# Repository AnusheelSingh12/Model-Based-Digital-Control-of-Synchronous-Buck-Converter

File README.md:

# Model-Based Design and HIL Deployment of a Cascade Digital Controller for a Synchronous Buck Converter on TI C2000 DSP

## Summer Research Internship

**Institution:** Indian Institute of Technology Guwahati

**Duration:** May 2026 – July 2026

---

# Overview

This repository documents my Summer Research Internship carried out at the Department of Electronics and Electrical Engineering, Indian Institute of Technology Guwahati.

The internship focused on the complete workflow involved in designing, simulating, implementing, and validating a digitally controlled synchronous buck converter using the Texas Instruments C2000 real-time digital signal processor platform.

Unlike repositories that present only the final implementation, this repository documents the complete engineering process, beginning with mathematical modeling and simulation, progressing through controller design, embedded firmware development, peripheral configuration, laboratory validation, and finally hardware deployment.

The project combines concepts from:

* Power Electronics
* Control Systems
* Embedded Systems
* Digital Signal Processing
* MATLAB & Simulink
* Simscape Electrical
* Real-Time Embedded Programming
* Hardware-in-the-Loop Development

---

# Project Objectives

The primary objectives of the internship were:

* Develop a high-fidelity digital twin of a synchronous buck converter.
* Design a cascaded digital controller consisting of outer voltage and inner current control loops.
* Learn the Texas Instruments C2000 development ecosystem.
* Implement embedded firmware using Code Composer Studio.
* Configure and validate DSP peripherals including GPIO, Timers, PWM, Interrupts, and ADC.
* Validate controller performance using laboratory instruments.
* Document the complete engineering workflow.

---

# Engineering Workflow

```text
Problem Definition
        │
        ▼
MATLAB Fundamentals
        │
        ▼
Simulink Fundamentals
        │
        ▼
Simscape Electrical
        │
        ▼
Digital Twin Development
        │
        ▼
Cascade PI Controller Design
        │
        ▼
Closed Loop Simulation
        │
        ▼
TI C2000 DSP Learning
        │
        ▼
GPIO
Interrupts
CPU Timers
PWM
ADC
        │
        ▼
Hardware Validation
        │
        ▼
Final System Integration
```

---

# Repository Structure

```text
IITG-DSP-Buck-Converter-Control/

├── 01_Internship_Overview/
│
├── 02_MATLAB_and_Simulink/
│
├── 03_Digital_Twin/
│
├── 04_Cascade_Controller/
│
├── 05_TI_C2000_DSP/
│   ├── GPIO/
│   ├── Interrupts/
│   ├── CPU_Timers/
│   ├── ePWM/
│   ├── ADC/
│
├── 06_Hardware_Setup/
│   ├── LaunchXL_F28379D/
│   ├── Oscilloscope/
│   ├── Function_Generator/
│
├── 07_Firmware/
│
├── 08_Simulation_Results/
│
├── 09_Final_Report/
│
├── Images/
│
├── Videos/
│
└── README.md
```

---

# Project Phases

## Phase 1 — Digital Twin Development

The first stage of the project focused on constructing a high-fidelity Simscape Electrical model of the synchronous buck converter.

Topics include:

* Converter topology
* MOSFET modelling
* Passive component modelling
* PWM generation
* Open-loop validation
* Converter analysis
* Duty-cycle experiments

---

## Phase 2 — Cascade Digital Controller

The second stage involved designing a cascaded digital controller.

Topics include:

* Voltage control loop
* Current control loop
* PI controller design
* Closed-loop regulation
* Controller tuning
* Performance analysis

---

## Phase 3 — TI C2000 DSP Development

The third stage focused on learning and implementing embedded firmware using the Texas Instruments C2000 platform.

Topics include:

* Code Composer Studio
* Project configuration
* GPIO
* Interrupts
* CPU Timers
* Enhanced PWM
* ADC
* Debugging
* Flash programming

---

## Phase 4 — Hardware Validation

The final stage focuses on validating both the firmware and control algorithms using laboratory equipment.

Topics include:

* Oscilloscope measurements
* Function generator experiments
* PWM verification
* ADC verification
* Peripheral testing
* System integration

---

# Software and Development Tools

MATLAB

Simulink

Simscape Electrical

Code Composer Studio

C2000Ware

Texas Instruments C2000 Driver Library

---

# Hardware Platform

Texas Instruments LaunchXL-F28379D

Texas Instruments C2000 DSP

Rigol Digital Oscilloscope

Function Generator

Host Computer

---

# Skills Developed

Throughout this internship I gained practical experience in:

* Model-Based Design
* Power Electronics
* Control Systems
* Digital Signal Processing
* MATLAB Programming
* Simulink Modelling
* Simscape Electrical
* Embedded C Programming
* TI C2000 Development
* Code Composer Studio
* GPIO Configuration
* Interrupt Programming
* CPU Timers
* PWM Generation
* ADC Configuration
* Oscilloscope Measurements
* Function Generator Operation
* Hardware Debugging
* Engineering Documentation

---

# Repository Navigation

| Section             | Description                                         |
| ------------------- | --------------------------------------------------- |
| Internship Overview | Internship objectives, timeline, and research scope |
| MATLAB and Simulink | Learning material and simulation fundamentals       |
| Digital Twin        | Simscape converter modelling                        |
| Cascade Controller  | Controller design and closed-loop simulation        |
| TI C2000 DSP        | Embedded firmware development                       |
| Hardware Setup      | Laboratory setup and instrumentation                |
| Firmware            | Embedded source code                                |
| Simulation Results  | Waveforms and experimental validation               |
| Final Report        | Internship report and documentation                 |

---

# Current Status

The repository is actively maintained and will continue to be updated throughout the internship.

Future updates include:

* Complete firmware
* Hardware validation
* Oscilloscope measurements
* ADC experiments
* Closed-loop implementation
* Final internship report
* Demonstration videos

---

# Acknowledgements

I would like to express my sincere gratitude to my internship supervisor, research mentors, and the School of Electronics and Electrical Engineering at the Indian Institute of Technology Guwahati for providing the opportunity to work on this project and gain practical experience in model-based design, embedded control systems, and real-time digital signal processing.

---

# Author

Anusheel Singh

Electronics and Communication Engineering

Areas of Interest

* Embedded Systems
* Digital Control Systems
* Power Electronics
* DSP
* Hardware Integration
* Robotics
* Automotive Electronics

---

This repository is intended to serve as a complete technical record of my internship, documenting both the engineering process and the final implementation.

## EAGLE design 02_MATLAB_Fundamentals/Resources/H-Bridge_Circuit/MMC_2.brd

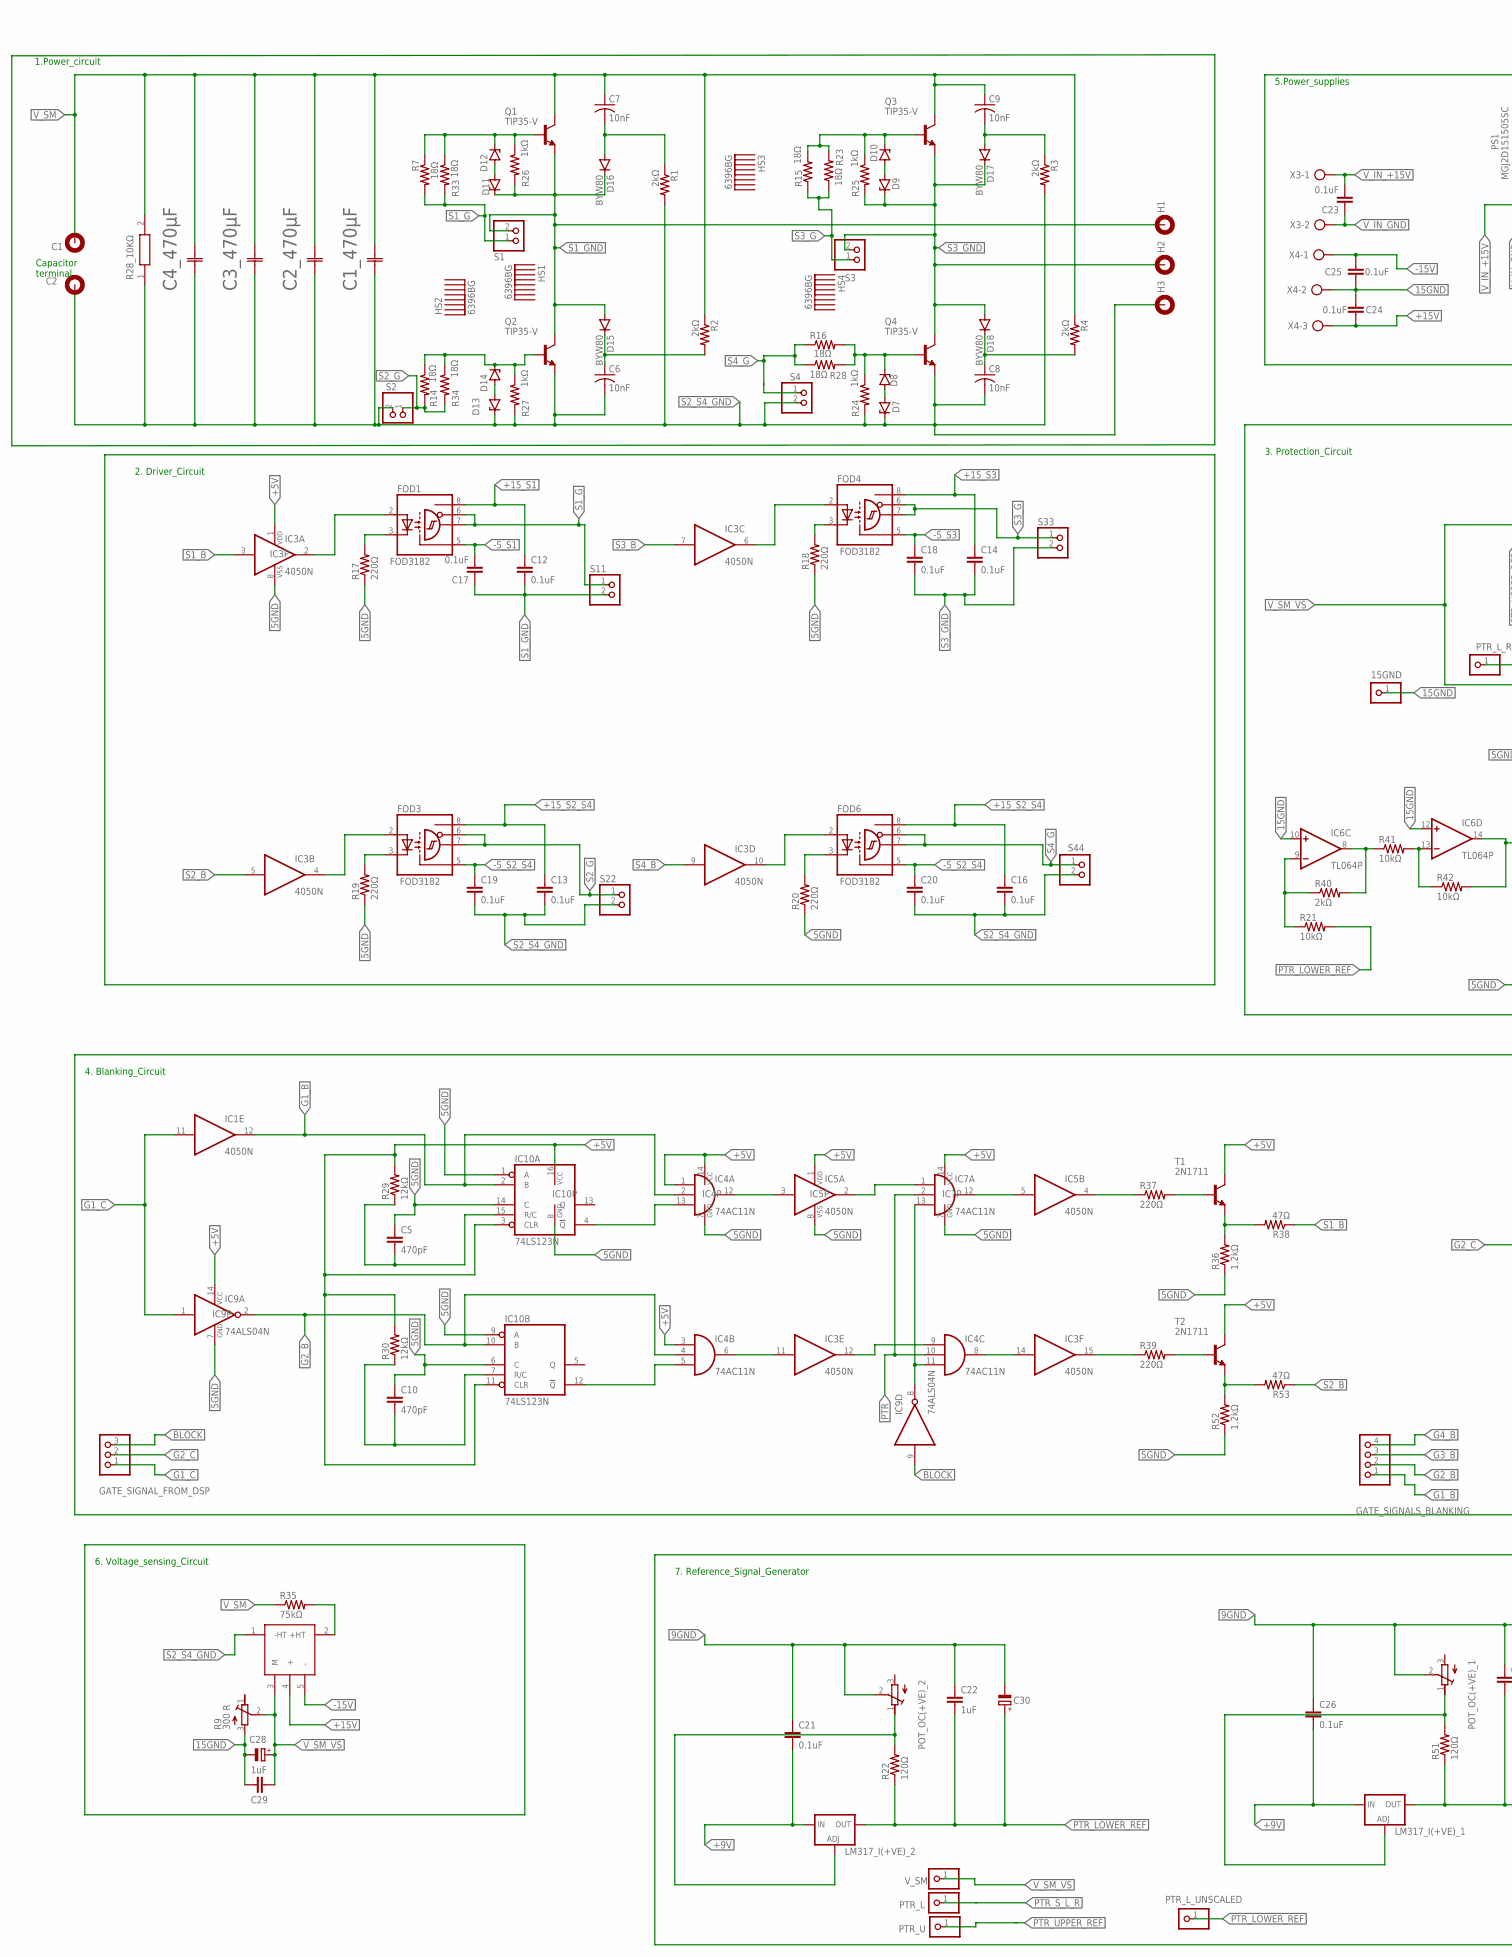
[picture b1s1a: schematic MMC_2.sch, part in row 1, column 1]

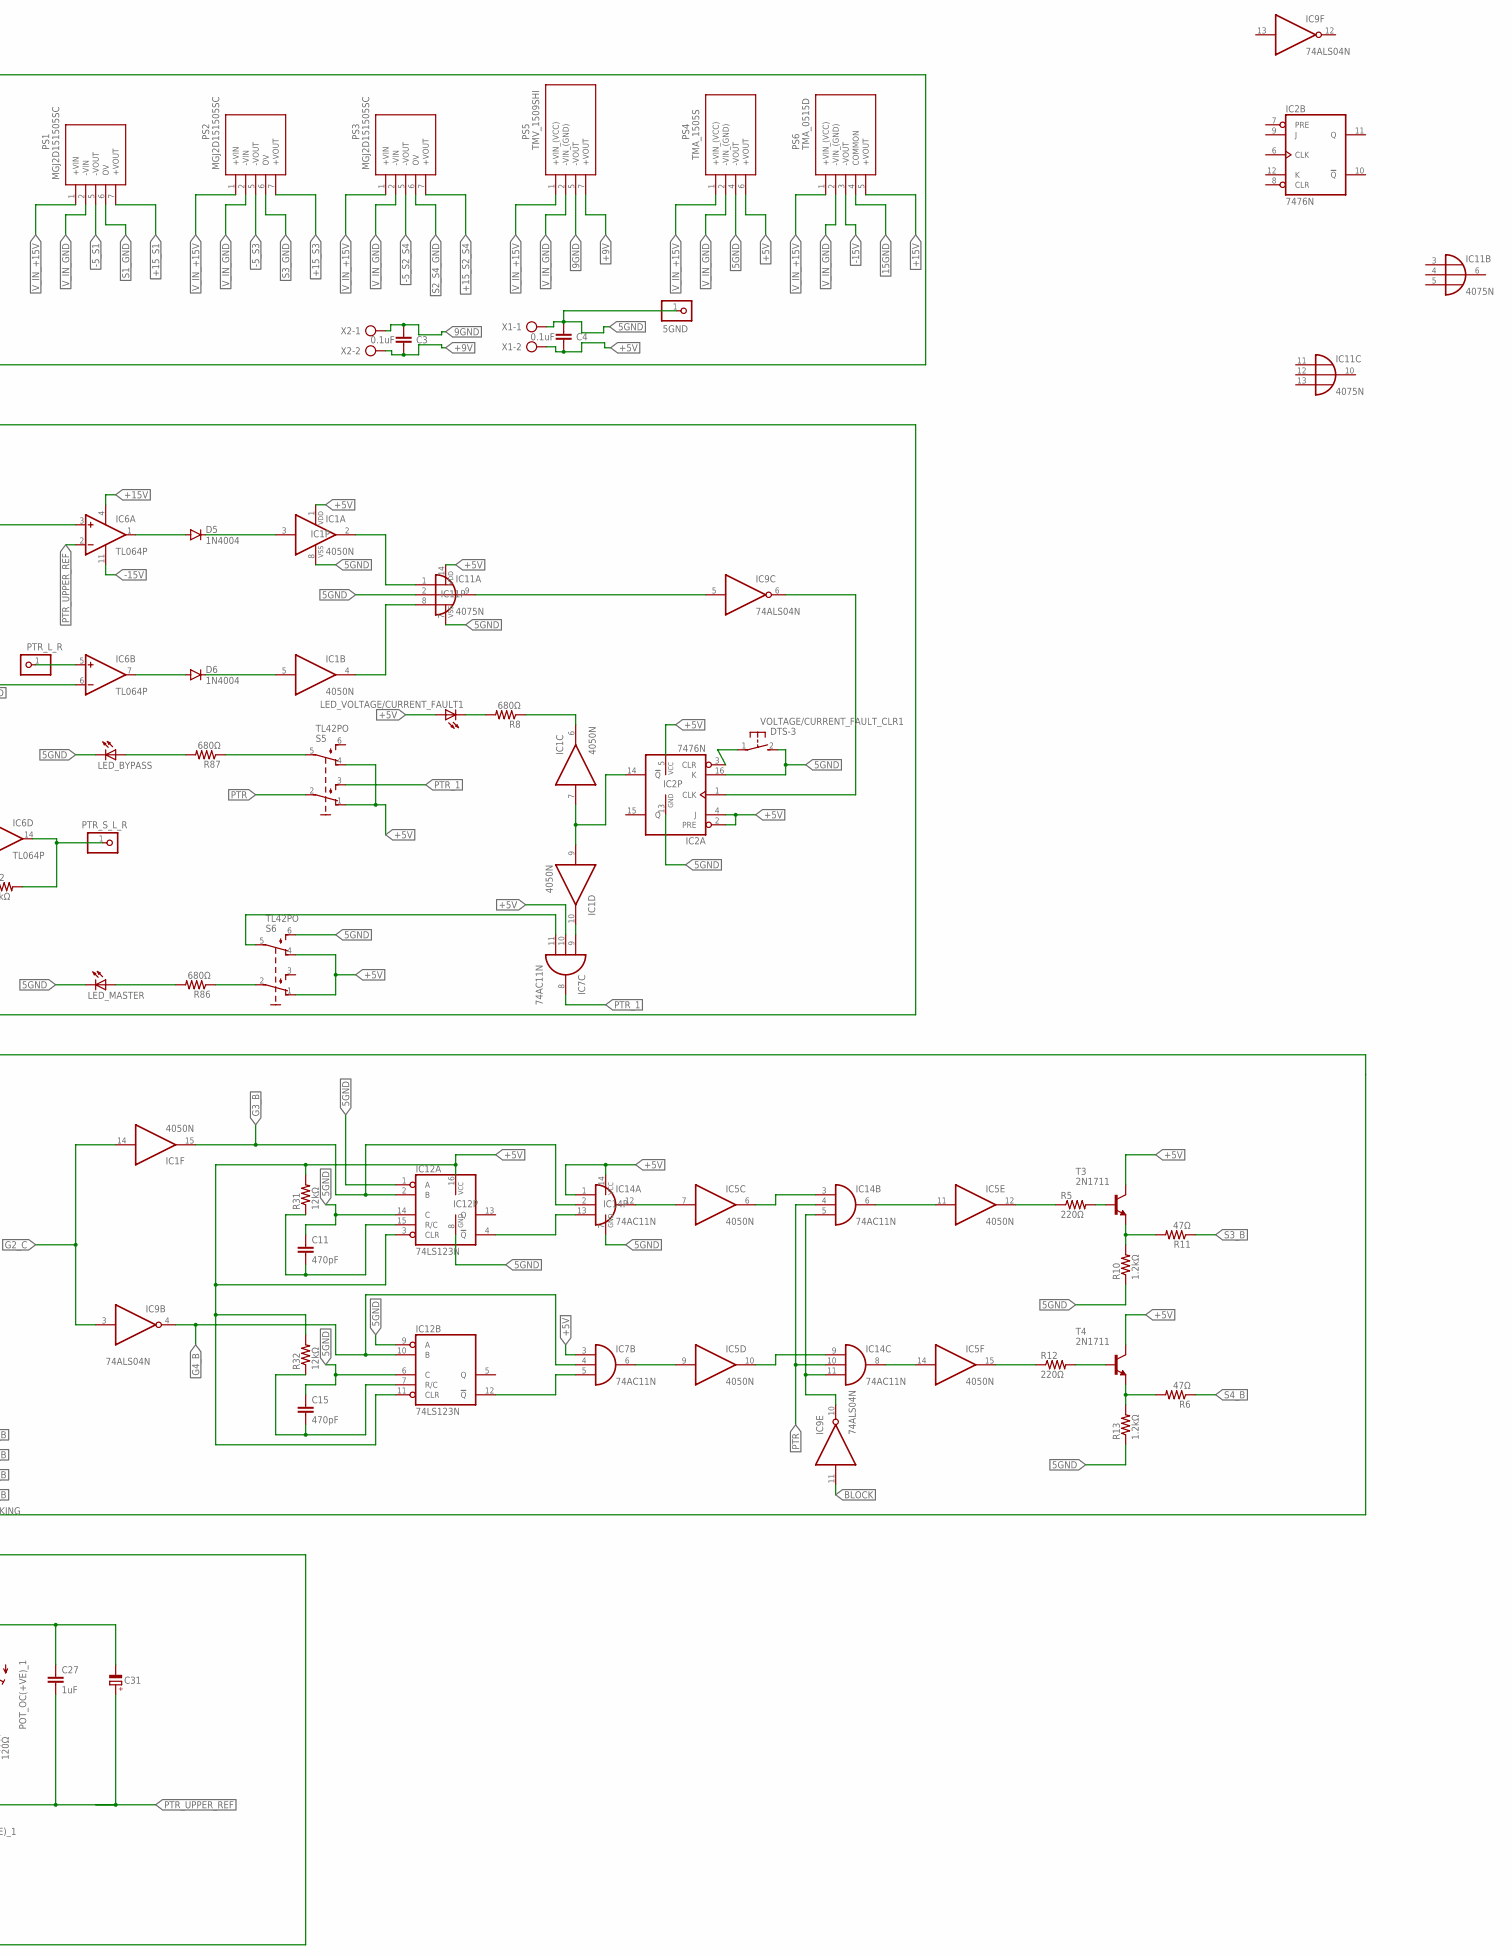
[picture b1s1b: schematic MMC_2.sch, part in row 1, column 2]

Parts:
5GND, 15GND: PINHD-1X1; 1X01
C1, C2: MOUNT-PAD-ROUND; 6-PAD
C1_470µF, C2_470µF, C3_470µF, C4_470µF: MAL215746471E3; CAP_2157_30X50_VIS
C3, C4, C12, C13, C14, C16, C17, C18, C19, C20, C21, C23, C24, C25, C26: 0.1uF; C025-025X050
C5, C10, C11, C15: 470pF; C025-025X050
C6, C7, C8, C9: 10nF; C150-054X183
C22, C27, C29: 1uF; C025-025X050
C28, C30, C31: CPOL-EUE2-4; E2-4
D5, D6: 1N4004; DO41-10
D7, D8, D9, D10, D11, D12, D13, D14: ZENER-DIODEDO35Z10; DO35Z10
D15, D16, D17, D18: BYW80; TO220ACS
FOD1, FOD3, FOD4, FOD6: FOD3182; DIL08
GATE_SIGNALS_BLANKING: PINHD-1X4; 1X04
GATE_SIGNAL_FROM_DSP: PINHD-1X3; 1X03
H1, H2, H3: MOUNT-PAD-ROUND; 6-PAD
HS1, HS2, HS3, HS4: 6396BG; HSINK_6396BG
IC1, IC3, IC5: 4050N; DIL16
IC2: 7476N; DIL16
IC4, IC7, IC14: 74AC11N; DIL14
IC6: TL064P; DIL14
IC8: LV25-P
IC9: 74ALS04N; DIL14
IC10, IC12: 74LS123N; DIL16
IC11: 4075N; DIL14
LED_BYPASS: LED3MM
LED_MASTER: LED3MM
LED_VOLTAGE/CURRENT_FAULT1: LED3MM
LM317_I(+VE)_1, LM317_I(+VE)_2: LM317TS; 317TS
POT_OC(+VE)_1, POT_OC(+VE)_2: R-TRIMMT93YA; RTRIMT93YA
PS1, PS2, PS3: MGJ2D151505SC
PS4: TMA_1505S; TMA0505S
PS5: TMV_1509SHI; TMV1512SHI
PS6: TMA_0515D; TMA0515D
PTR_L: PINHD-1X1; 1X01
PTR_L_R: PINHD-1X1; 1X01
PTR_L_UNSCALED: PINHD-1X1; 1X01
PTR_S_L_R: PINHD-1X1; 1X01
PTR_U: PINHD-1X1; 1X01
Q1, Q2, Q3, Q4: TIP35-V; TO247-V
R1, R2, R3, R4: 2kΩ; 0414/15
R5, R12, R17, R18, R19, R20, R37, R39: 220Ω; 0207/10
R6, R11, R38, R53: 47Ω; 0207/10
R7, R14, R15, R16, R23, R28, R33, R34: 18Ω; 0207/10
R8, R86, R87: 680Ω; 0207/10
R9: 300 R; RTRIMT93YA
R10, R13, R36, R52: 1.2kΩ; 0207/10
R21, R41, R42: 10kΩ; 0207/10
R22, R51: 120Ω; 0207/10
R24, R25, R26, R27: 1kΩ; 0207/10
R28_10KΩ: SBCHE610KJ
R29, R30, R31, R32: 12kΩ; 0207/10
R35: 75kΩ; 0411/15
R40: 2kΩ; 0207/10
S1, S2, S3, S4, S11, S22, S33, S44: PINHD-1X2; 1X02
S5, S6: TL42PO; TL4XPO
T1, T2, T3, T4: 2N1711; TO39
VOLTAGE/CURRENT_FAULT_CLR1: DTS-3
V_SM: PINHD-1X1; 1X01
X1, X2, X3: AK300/2
X4: AK300/3

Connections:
5GND: 5GND.1, C4.2, C5.1, C10.1, C11.1, C15.1, IC1.8 (VSS), IC2.13 (GND), IC2.16 (K), IC3.8 (VSS), IC4.7 (GND), IC5.8 (VSS), IC7.7 (GND), IC9.7 (GND), IC10.1 (A), IC10.6 (C), IC10.8 (GND), IC10.9 (A), IC10.14 (C), IC11.2 (I1), IC11.7 (VSS), IC12.1 (A), IC12.6 (C), IC12.8 (GND), IC12.9 (A), IC12.14 (C), IC14.7 (GND), LED_BYPASS.K (C), LED_MASTER.K (C), PS4.4 (-VOUT), R10.1, R13.1, R17.1, R18.1, R19.1, R20.1, R36.1, R52.1, S6.6 (S1), VOLTAGE/CURRENT_FAULT_CLR1.2, X1.1
9GND: C3.2, C21.1, C22.1, C26.1, C27.1, C30.-, C31.-, POT_OC(+VE)_1.2 (S), POT_OC(+VE)_2.2 (S), PS5.5 (-VOUT), X2.1
15GND: 15GND.1, C24.2, C25.2, C28.-, C29.2, IC6.10 (+IN), IC6.12 (+IN), PS6.4 (COMMON), R9.3 (A), X4.2
+5V: C4.1, IC1.1 (VDD), IC2.2 (PRE), IC2.4 (J), IC2.5 (VCC), IC3.1 (VDD), IC4.1 (I0), IC4.3 (I0), IC4.14 (VCC), IC5.1 (VDD), IC7.3 (I0), IC7.10 (I1), IC7.14 (VCC), IC9.14 (VCC), IC10.3 (CLR), IC10.11 (CLR), IC10.16 (VCC), IC11.14 (VDD), IC12.3 (CLR), IC12.11 (CLR), IC12.16 (VCC), IC14.1 (I0), IC14.14 (VCC), LED_VOLTAGE/CURRENT_FAULT1.A, PS4.6 (+VOUT), R29.2, R30.2, R31.2, R32.2, S5.1 (O), S5.4 (O1), S6.1 (O), S6.4 (O1), T1.3 (C), T2.3 (C), T3.3 (C), T4.3 (C), X1.2
+9V: C3.1, C21.2, C26.2, LM317_I(+VE)_1.3 (IN), LM317_I(+VE)_2.3 (IN), PS5.7 (+VOUT), X2.2
+15V: C24.1, IC6.4 (V+), IC8.4 (+), PS6.5 (+VOUT), X4.3
+15_S1: C12.1, FOD1.8 (VCC), PS1.7 (+VOUT)
+15_S2_S4: C13.1, C16.1, FOD3.8 (VCC), FOD6.8 (VCC), PS3.7 (+VOUT)
+15_S3: C14.1, FOD4.8 (VCC), PS2.7 (+VOUT)
-5_S1: C17.2, FOD1.5 (GND), PS1.5 (-VOUT)
-5_S2_S4: C19.1, C20.1, FOD3.5 (GND), FOD6.5 (GND), PS3.5 (-VOUT)
-5_S3: C18.1, FOD4.5 (GND), PS2.5 (-VOUT)
-15V: C25.1, IC6.11 (V-), IC8.5 (-), PS6.3 (-VOUT), X4.1
AA: D12.C, Q1.1 (B), R7.1, R26.1, R33.1
BLOCK: GATE_SIGNAL_FROM_DSP.3, IC9.9 (I), IC9.11 (I)
G1_B: GATE_SIGNALS_BLANKING.1, IC1.12 (O), IC4.2 (I1), IC10.2 (B)
G1_C: GATE_SIGNAL_FROM_DSP.1, IC1.11 (I), IC9.1 (I)
G2_B: GATE_SIGNALS_BLANKING.2, IC4.4 (I1), IC9.2 (O), IC10.10 (B)
G2_C: GATE_SIGNAL_FROM_DSP.2, IC1.14 (I), IC9.3 (I)
G3_B: GATE_SIGNALS_BLANKING.3, IC1.15 (O), IC12.2 (B), IC14.2 (I1)
G4_B: GATE_SIGNALS_BLANKING.4, IC7.4 (I1), IC9.4 (O), IC12.10 (B)
GND(5): FOD3.3 (C), R19.2
unnamed: FOD1.2 (A), IC3.2 (O)
unnamed: D8.C, Q4.1 (B), R16.2, R24.1, R28.2
unnamed: D10.C, Q3.1 (B), R15.2, R23.2, R25.1
unnamed: IC7.11 (I2), S6.5 (P1)
unnamed: D5.A, IC6.1 (OUT)
unnamed: IC1.10 (O), IC7.9 (I0)
unnamed: C9.2, D17.A, R3.1
unnamed: IC12.4 (!Q), IC14.13 (I2)
unnamed: IC5.7 (I), IC14.12 (O)
unnamed: IC5.6 (O), IC14.3 (I0)
unnamed: IC5.11 (I), IC14.6 (O)
unnamed: IC5.12 (O), R5.1
unnamed: R5.2, T3.2 (B)
unnamed: C8.1, D18.C, R4.2
unnamed: R10.2, R11.2, T3.1 (E)
unnamed: IC5.15 (O), R12.1
unnamed: C6.1, D15.C, R2.2
unnamed: FOD3.2 (A), IC3.4 (O)
unnamed: FOD4.2 (A), IC3.6 (O)
unnamed: FOD6.2 (A), IC3.10 (O)
unnamed: FOD1.3 (C), R17.2
unnamed: FOD4.3 (C), R18.2
unnamed: FOD6.3 (C), R20.2
unnamed: R12.2, T4.2 (B)
unnamed: R6.2, R13.2, T4.1 (E)
unnamed: D5.C, IC1.3 (I)
unnamed: IC5.5 (I), IC7.12 (O)
unnamed: IC4.11 (I2), IC7.13 (I2), IC9.8 (O)
unnamed: IC7.5 (I2), IC12.12 (!Q)
unnamed: IC5.9 (I), IC7.6 (O)
unnamed: IC5.10 (O), IC14.9 (I0)
unnamed: IC9.10 (O), IC14.5 (I2), IC14.11 (I2)
unnamed: IC5.14 (I), IC14.8 (O)
unnamed: IC6.5 (+IN), PTR_L_R.1
unnamed: IC8.2 (+HT), R35.2
unnamed: LM317_I(+VE)_1.1 (ADJ), POT_OC(+VE)_1.1 (E), R51.2
unnamed: C7.2, D16.A, R1.1
unnamed: IC6.9 (-IN), R21.1, R40.1
unnamed: IC6.8 (OUT), R40.2, R41.1
unnamed: D7.A, D8.A
unnamed: D9.A, D10.A
unnamed: D11.A, D12.A
unnamed: D13.A, D14.A
unnamed: IC9.5 (I), IC11.9 (O)
unnamed: IC6.13 (-IN), R41.2, R42.1
unnamed: IC1.2 (O), IC11.1 (I0)
unnamed: D6.A, IC6.7 (OUT)
unnamed: IC1.4 (O), IC11.8 (I2)
unnamed: D6.C, IC1.5 (I)
unnamed: LM317_I(+VE)_2.1 (ADJ), POT_OC(+VE)_2.1 (E), R22.2
unnamed: IC2.1 (CLK), IC9.6 (O)
unnamed: IC1.6 (O), R8.1
unnamed: LED_VOLTAGE/CURRENT_FAULT1.K (C), R8.2
unnamed: IC2.3 (CLR), VOLTAGE/CURRENT_FAULT_CLR1.1
unnamed: C5.2, IC10.15 (R/C), R29.1
unnamed: C10.2, IC10.7 (R/C), R30.1
unnamed: C11.2, IC12.15 (R/C), R31.1
unnamed: IC4.13 (I2), IC10.4 (!Q)
unnamed: IC4.12 (O), IC5.3 (I)
unnamed: IC5.2 (O), IC7.1 (I0)
unnamed: IC5.4 (O), R37.1
unnamed: R37.2, T1.2 (B)
unnamed: R36.2, R38.2, T1.1 (E)
unnamed: IC3.15 (O), R39.1
unnamed: R39.2, T2.2 (B)
unnamed: R52.2, R53.2, T2.1 (E)
unnamed: IC4.5 (I2), IC10.12 (!Q)
unnamed: IC3.11 (I), IC4.6 (O)
unnamed: IC3.12 (O), IC4.9 (I0)
unnamed: IC3.14 (I), IC4.8 (O)
unnamed: C15.2, IC12.7 (R/C), R32.1
unnamed: R86.1, S6.2
unnamed: LED_MASTER.A, R86.2
unnamed: R87.1, S5.5 (P1)
unnamed: LED_BYPASS.A, R87.2
PTR: IC4.10 (I1), IC7.2 (I1), IC14.4 (I1), IC14.10 (I1), S5.2
PTR_1: IC7.8 (O), S5.3 (S)
PTR_LOWER_REF: C22.2, C30.+, LM317_I(+VE)_2.2 (OUT), PTR_L_UNSCALED.1, R21.2, R22.1
PTR_S_L_R: IC6.14 (OUT), PTR_L.1, PTR_S_L_R.1, R42.2
PTR_UPPER_REF: C27.2, C31.+, IC6.2 (-IN), LM317_I(+VE)_1.2 (OUT), PTR_U.1, R51.1
Q_BAR: IC1.7 (I), IC1.9 (I), IC2.14 (!Q)
S1_B: IC3.3 (I), R38.1
S1_G: FOD1.6 (VE), FOD1.7 (VO), R7.2, R33.2, S1.1, S11.1
S1_GND: C12.2, C17.1, D11.C, D15.A, D16.C, H1.B5,5, PS1.6 (OV), Q1.3 (E), Q2.2 (C), R26.2, S1.2, S11.2
S2_B: IC3.5 (I), R53.1
S2_G: FOD3.6 (VE), FOD3.7 (VO), R14.2, R34.2, S2.1, S22.1
S2_S4_GND: C1_470µF.1, C2.B5,5, C2_470µF.1, C3_470µF.1, C4_470µF.1, C6.2, C8.2, C13.2, C16.2, C19.2, C20.2, D7.C, D13.C, H3.B5,5, IC8.1 (-HT), PS3.6 (OV), Q2.3 (E), Q4.3 (E), R1.2, R3.2, R24.2, R27.2, R28_10KΩ.1, S2.2, S4.2, S22.2, S44.2
S3_B: IC3.7 (I), R11.1
S3_G: FOD4.6 (VE), FOD4.7 (VO), R15.1, R23.1, S3.1, S33.1
S3_GND: C14.2, C18.2, D9.C, D17.C, D18.A, H2.B5,5, PS2.6 (OV), Q3.3 (E), Q4.2 (C), R25.2, S3.2, S33.2
S4_B: IC3.9 (I), R6.1
S4_G: FOD6.6 (VE), FOD6.7 (VO), R16.1, R28.1, S4.1, S44.1
S222: D14.C, Q2.1 (B), R14.1, R27.1, R34.1
V_IN_+15V: C23.2, PS1.1 (+VIN), PS2.1 (+VIN), PS3.1 (+VIN), PS4.1 (+VIN_(VCC)), PS5.1 (+VIN_(VCC)), PS6.1 (+VIN_(VCC)), X3.1
V_IN_GND: C23.1, PS1.2 (-VIN), PS2.2 (-VIN), PS3.2 (-VIN), PS4.2 (-VIN_(GND)), PS5.2 (-VIN_(GND)), PS6.2 (-VIN_(GND)), X3.2
V_SM: C1.B5,5, C1_470µF.2, C2_470µF.2, C3_470µF.2, C4_470µF.2, C7.1, C9.1, Q1.2 (C), Q3.2 (C), R2.1, R4.1, R28_10KΩ.2, R35.1
V_SM_VS: C28.+, C29.1, IC6.3 (+IN), IC6.6 (-IN), IC8.3 (M), R9.2 (S), V_SM.1

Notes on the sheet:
5.Power_supplies
1.Power_circuit
2. Driver_Circuit
3. Protection_Circuit
4. Blanking_Circuit
6. Voltage_sensing_Circuit
7. Reference_Signal_Generator
Capacitor terminal

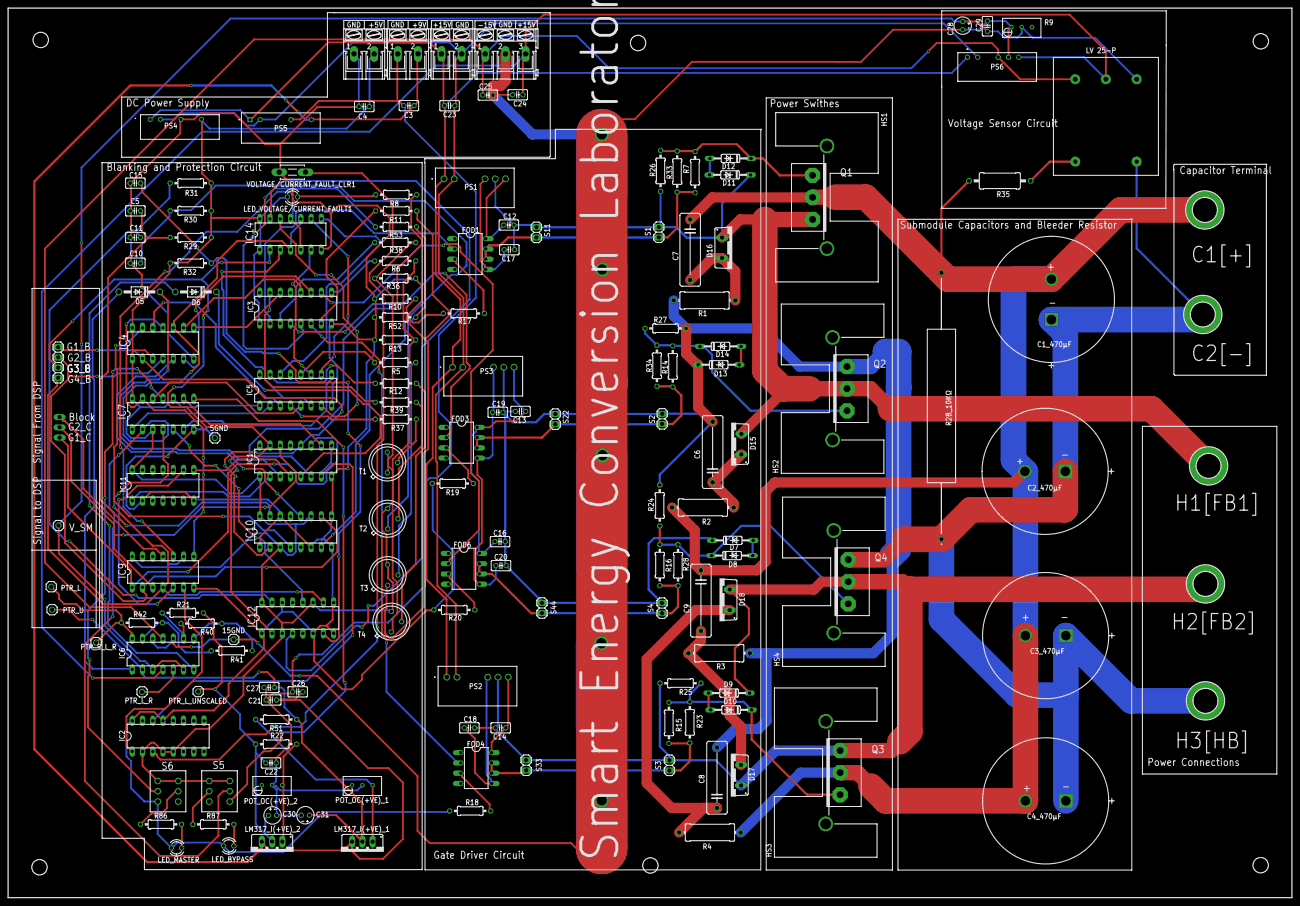
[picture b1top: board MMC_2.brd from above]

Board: 2 copper layers, 317.9 x 220.2 mm, 167 parts (1 on the bottom side), 119 nets.

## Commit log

2026-06-29 Revise README for project clarity and detail
    Updated the README to reflect the project title, internship details, and comprehensive overview of the engineering workflow and objectives.
2026-06-30 Update-1
2026-06-30 Added MATLAB and Simulink Work
2026-06-30 Added Digital Twin Files
2026-06-30 Initial commit for firmware
2026-06-30 Created folder structure for Firmware folder
2026-06-30 Added GPIO work and examples
2026-06-30 Added CPU_Timer examples
2026-06-30 Added ePWM example and study
2026-06-30 Added Final Controller Files
2026-06-30 Added eaxmple learning
